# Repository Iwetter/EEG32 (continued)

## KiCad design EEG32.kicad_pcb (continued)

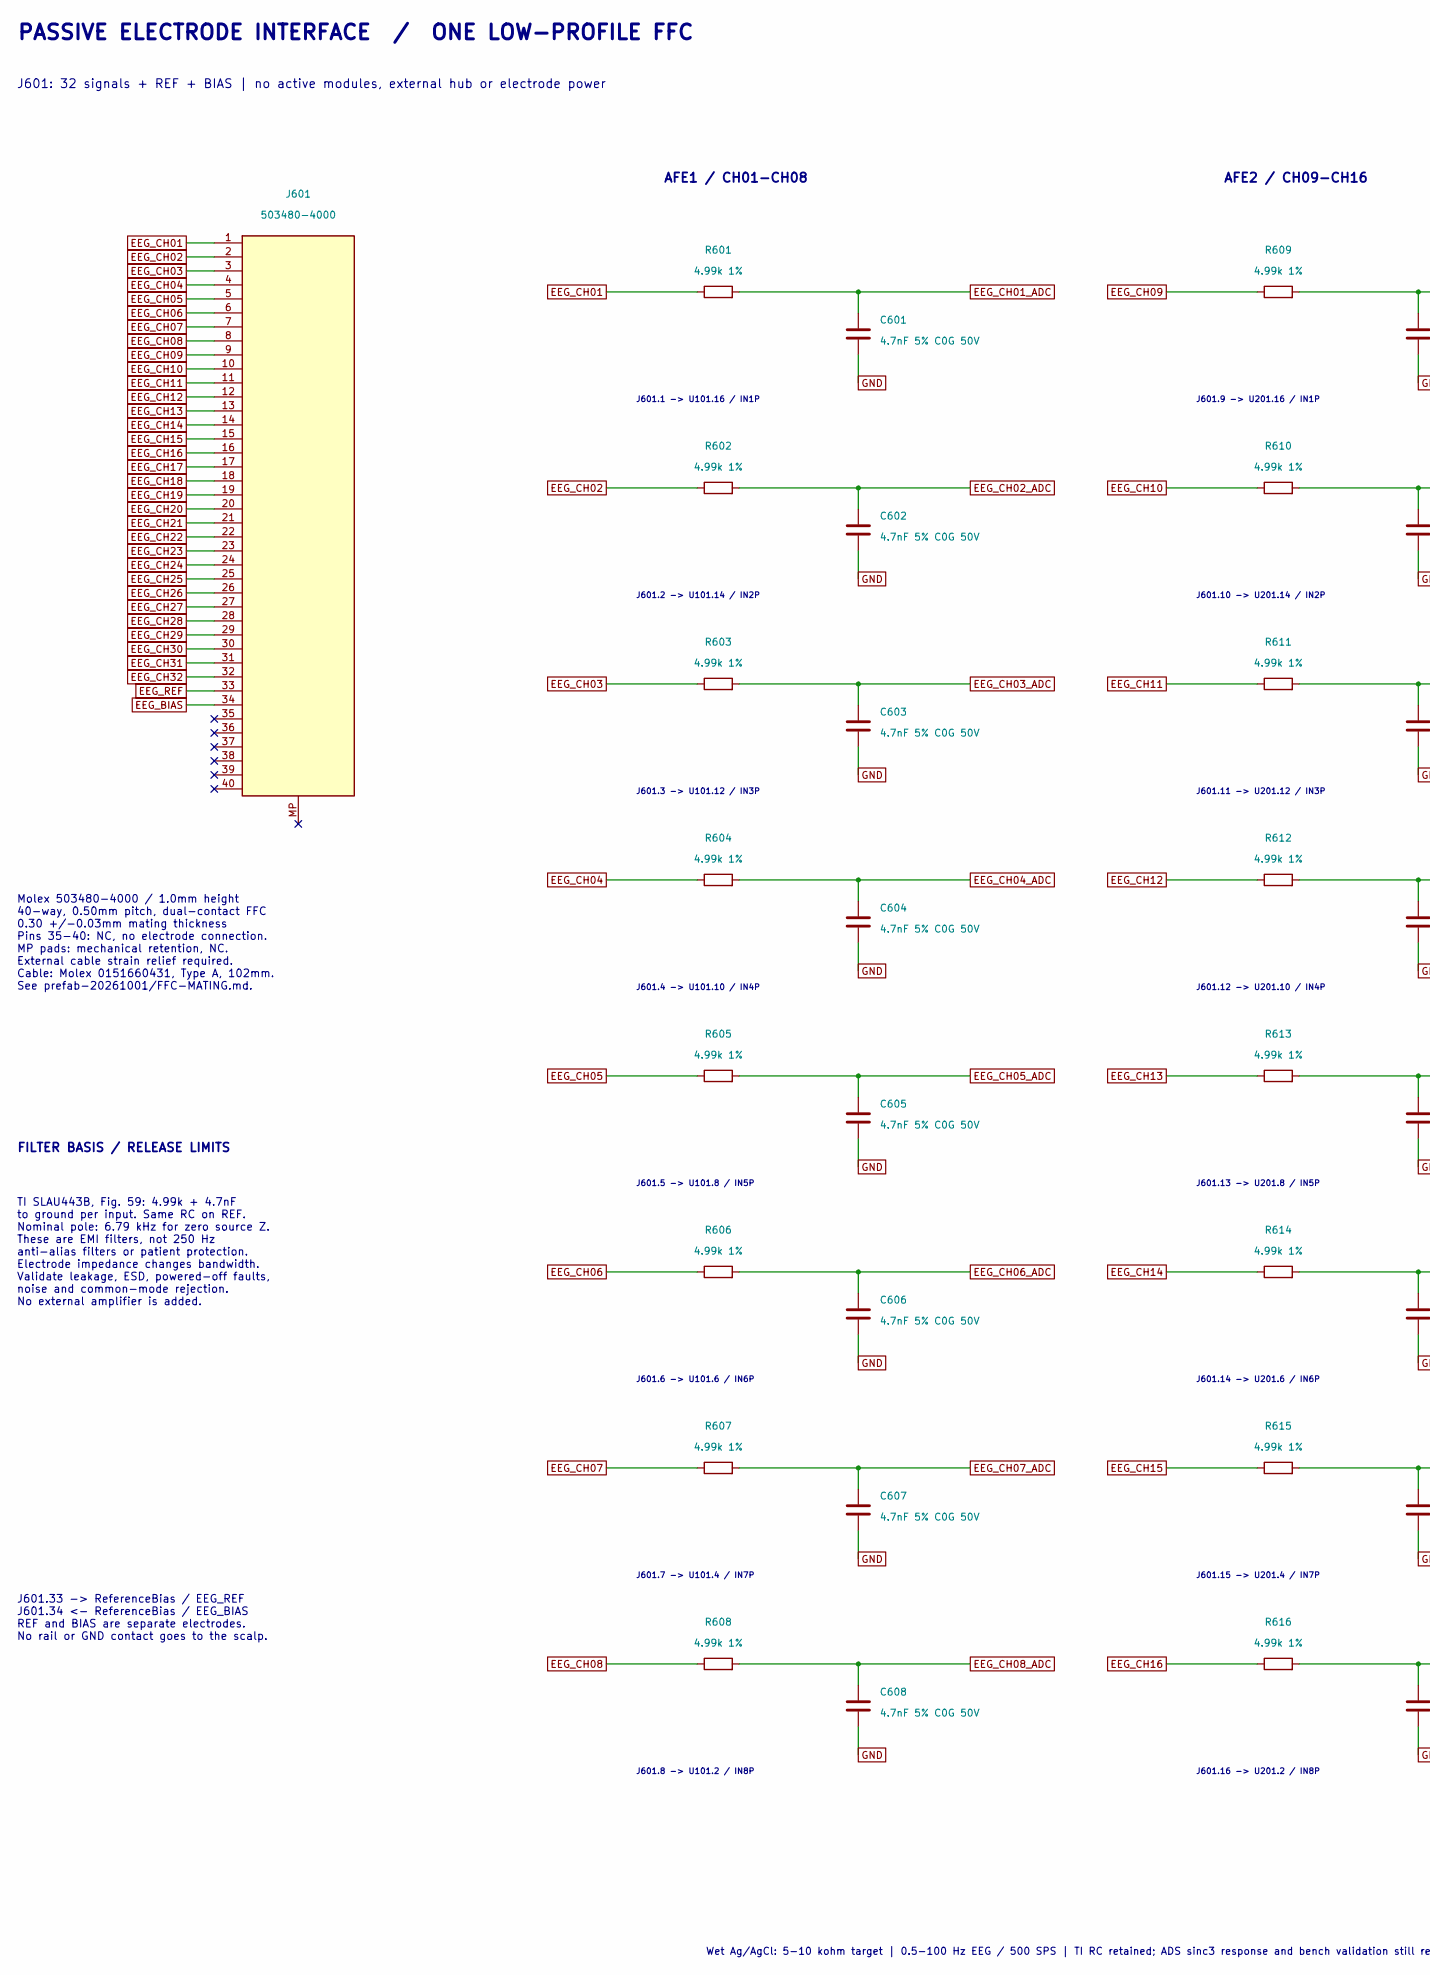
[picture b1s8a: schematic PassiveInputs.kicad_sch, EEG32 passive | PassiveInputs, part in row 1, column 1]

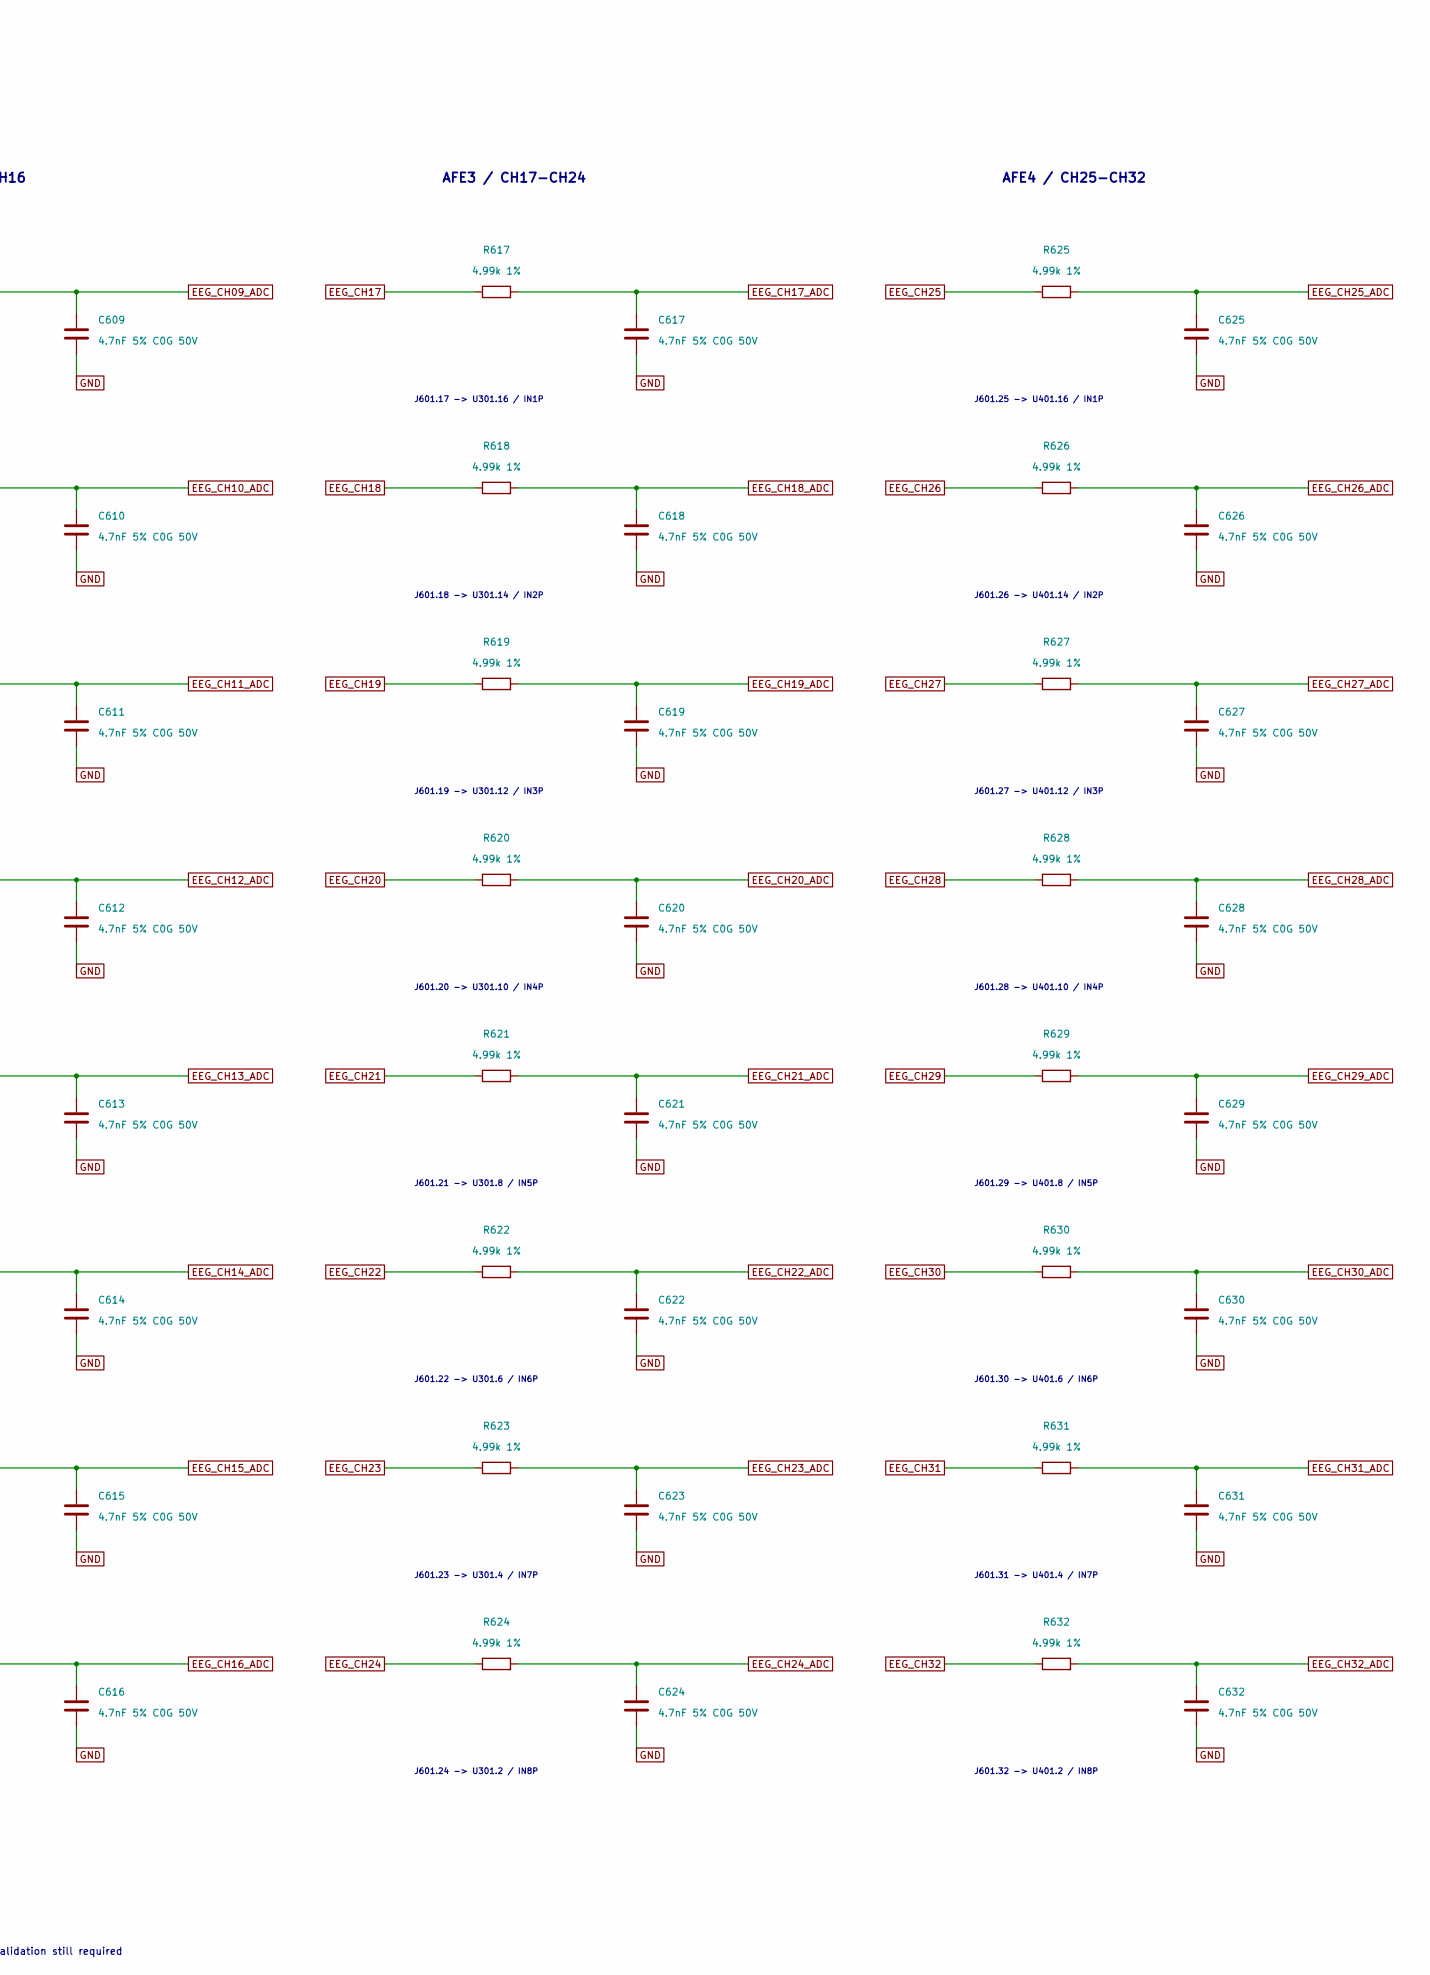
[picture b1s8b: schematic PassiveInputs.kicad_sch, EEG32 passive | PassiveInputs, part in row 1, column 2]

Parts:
C601, C602, C603, C604, C605, C606, C607, C608, C609, C610, C611, C612, C613, C614, C615, C616, C617, C618, C619, C620, C621, C622, C623, C624, C625, C626, C627, C628, C629, C630, C631, C632: 4.7nF 5% C0G 50V; C0603; MPN GRM1885C1H472JA01D
J601: 503480-4000; Molex_503480-4000_1x40_P0.50mm_Horizontal; MPN 503480-4000
R601, R602, R603, R604, R605, R606, R607, R608, R609, R610, R611, R612, R613, R614, R615, R616, R617, R618, R619, R620, R621, R622, R623, R624, R625, R626, R627, R628, R629, R630, R631, R632: 4.99k 1%; R0402; MPN RC0402FR-074K99L

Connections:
EEG_BIAS: J601.34; also elsewhere on the board
EEG_CH01: J601.1, R601.1
EEG_CH01_ADC: C601.1, R601.2; also elsewhere on the board
EEG_CH02: J601.2, R602.1
EEG_CH02_ADC: C602.1, R602.2; also elsewhere on the board
EEG_CH03: J601.3, R603.1
EEG_CH03_ADC: C603.1, R603.2; also elsewhere on the board
EEG_CH04: J601.4, R604.1
EEG_CH04_ADC: C604.1, R604.2; also elsewhere on the board
EEG_CH05: J601.5, R605.1
EEG_CH05_ADC: C605.1, R605.2; also elsewhere on the board
EEG_CH06: J601.6, R606.1
EEG_CH06_ADC: C606.1, R606.2; also elsewhere on the board
EEG_CH07: J601.7, R607.1
EEG_CH07_ADC: C607.1, R607.2; also elsewhere on the board
EEG_CH08: J601.8, R608.1
EEG_CH08_ADC: C608.1, R608.2; also elsewhere on the board
EEG_CH09: J601.9, R609.1
EEG_CH09_ADC: C609.1, R609.2; also elsewhere on the board
EEG_CH10: J601.10, R610.1
EEG_CH10_ADC: C610.1, R610.2; also elsewhere on the board
EEG_CH11: J601.11, R611.1
EEG_CH11_ADC: C611.1, R611.2; also elsewhere on the board
EEG_CH12: J601.12, R612.1
EEG_CH12_ADC: C612.1, R612.2; also elsewhere on the board
EEG_CH13: J601.13, R613.1
EEG_CH13_ADC: C613.1, R613.2; also elsewhere on the board
EEG_CH14: J601.14, R614.1
EEG_CH14_ADC: C614.1, R614.2; also elsewhere on the board
EEG_CH15: J601.15, R615.1
EEG_CH15_ADC: C615.1, R615.2; also elsewhere on the board
EEG_CH16: J601.16, R616.1
EEG_CH16_ADC: C616.1, R616.2; also elsewhere on the board
EEG_CH17: J601.17, R617.1
EEG_CH17_ADC: C617.1, R617.2; also elsewhere on the board
EEG_CH18: J601.18, R618.1
EEG_CH18_ADC: C618.1, R618.2; also elsewhere on the board
EEG_CH19: J601.19, R619.1
EEG_CH19_ADC: C619.1, R619.2; also elsewhere on the board
EEG_CH20: J601.20, R620.1
EEG_CH20_ADC: C620.1, R620.2; also elsewhere on the board
EEG_CH21: J601.21, R621.1
EEG_CH21_ADC: C621.1, R621.2; also elsewhere on the board
EEG_CH22: J601.22, R622.1
EEG_CH22_ADC: C622.1, R622.2; also elsewhere on the board
EEG_CH23: J601.23, R623.1
EEG_CH23_ADC: C623.1, R623.2; also elsewhere on the board
EEG_CH24: J601.24, R624.1
EEG_CH24_ADC: C624.1, R624.2; also elsewhere on the board
EEG_CH25: J601.25, R625.1
EEG_CH25_ADC: C625.1, R625.2; also elsewhere on the board
EEG_CH26: J601.26, R626.1
EEG_CH26_ADC: C626.1, R626.2; also elsewhere on the board
EEG_CH27: J601.27, R627.1
EEG_CH27_ADC: C627.1, R627.2; also elsewhere on the board
EEG_CH28: J601.28, R628.1
EEG_CH28_ADC: C628.1, R628.2; also elsewhere on the board
EEG_CH29: J601.29, R629.1
EEG_CH29_ADC: C629.1, R629.2; also elsewhere on the board
EEG_CH30: J601.30, R630.1
EEG_CH30_ADC: C630.1, R630.2; also elsewhere on the board
EEG_CH31: J601.31, R631.1
EEG_CH31_ADC: C631.1, R631.2; also elsewhere on the board
EEG_CH32: J601.32, R632.1
EEG_CH32_ADC: C632.1, R632.2; also elsewhere on the board
EEG_REF: J601.33; also elsewhere on the board
GND: C601.2, C602.2, C603.2, C604.2, C605.2, C606.2, C607.2, C608.2, C609.2, C610.2, C611.2, C612.2, C613.2, C614.2, C615.2, C616.2, C617.2, C618.2, C619.2, C620.2, C621.2, C622.2, C623.2, C624.2, C625.2, C626.2, C627.2, C628.2, C629.2, C630.2, C631.2, C632.2; also elsewhere on the board

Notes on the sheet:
PASSIVE ELECTRODE INTERFACE / ONE LOW-PROFILE FFC
J601: 32 signals + REF + BIAS | no active modules, external hub or electrode power
Molex 503480-4000 / 1.0mm height 40-way, 0.50mm pitch, dual-contact FFC 0.30 +/-0.03mm mating thickness Pins 35-40: NC, no electrode connection. MP pads: mechanical retention, NC. External cable strain relief required. Cable: Molex 0151660431, Type A, 102mm. See prefab-20261001/FFC-MATING.md.
FILTER BASIS / RELEASE LIMITS
TI SLAU443B, Fig. 59: 4.99k + 4.7nF to ground per input. Same RC on REF. Nominal pole: 6.79 kHz for zero source Z. These are EMI filters, not 250 Hz anti-alias filters or patient protection. Electrode impedance changes bandwidth. Validate leakage, ESD, powered-off faults, noise and common-mode reje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
J601.33 -> ReferenceBias / EEG_REF J601.34 <- ReferenceBias / EEG_BIAS REF and BIAS are separate electrodes. No rail or GND contact goes to the scalp.
AFE1 / CH01-CH08
J601.1 -> U101.16 / IN1P
J601.2 -> U101.14 / IN2P
J601.3 -> U101.12 / IN3P
J601.4 -> U101.10 / IN4P
J601.5 -> U101.8 / IN5P
J601.6 -> U101.6 / IN6P
J601.7 -> U101.4 / IN7P
J601.8 -> U101.2 / IN8P
AFE2 / CH09-CH16
J601.9 -> U201.16 / IN1P
J601.10 -> U201.14 / IN2P
J601.11 -> U201.12 / IN3P
J601.12 -> U201.10 / IN4P
J601.13 -> U201.8 / IN5P
J601.14 -> U201.6 / IN6P
J601.15 -> U201.4 / IN7P
J601.16 -> U201.2 / IN8P
AFE3 / CH17-CH24
J601.17 -> U301.16 / IN1P
J601.18 -> U301.14 / IN2P
J601.19 -> U301.12 / IN3P
J601.20 -> U301.10 / IN4P
J601.21 -> U301.8 / IN5P
J601.22 -> U301.6 / IN6P
J601.23 -> U301.4 / IN7P
J601.24 -> U301.2 / IN8P
AFE4 / CH25-CH32
J601.25 -> U401.16 / IN1P
J601.26 -> U401.14 / IN2P
J601.27 -> U401.12 / IN3P
J601.28 -> U401.10 / IN4P
J601.29 -> U401.8 / IN5P
J601.30 -> U401.6 / IN6P

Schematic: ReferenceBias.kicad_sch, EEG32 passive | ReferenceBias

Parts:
C633: 4.7nF 5% C0G 50V; C0603; MPN GRM1885C1H472JA01D
R633, R634: 4.99k 1%; R0402; MPN RC0402FR-074K99L

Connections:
BIAS_DRIVE: R634.1; also elsewhere on the board
EEG_BIAS: R634.2; also elsewhere on the board
EEG_REF: R633.1; also elsewhere on the board
EEG_REF_ADC: C633.1, R633.2; also elsewhere on the board
GND: C633.2; also elsewhere on the board

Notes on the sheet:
SHARED REF / SEPARATE BIAS
Passive common-reference montage. No local electrode buffers; no REF/BIAS short.
J601.33 / passive REF
U101/U201/U301/U401: pin 17 / SRB1 MISC1.SRB1 = 1; SRB2 remains unused. TP7 measures the filtered shared reference.
Unbuffered shared REF retained: validate aggregate input loading and lead-off configuration for 32 channels. One common REF filter; do not add 32 parallel filter capacitors to this electrode. TI EVM default directly selects REF_ELEC to SRB1 (JP8); its optional buffer is not populated here.
U101 BIASOUT, pin 63 Existing 1M || 1nF feedback remains before R634.
J601.34 / separate BIAS electrode 4.99k is TI EVM R10 value; it is not a validated patient-current limiter.
FIRMWARE + VALIDATION
Enable only U101 BIAS amplifier; slave BIASOUT pins remain NC. Preserve shared BIAS_SUM and BIASIN. Select BIAS sense channels deliberately. Validate stability with electrode/cable impedance and disconnect faults. At +5VA, internal BIASREF targets mid-supply. REF is neither GND nor the ADS VREFP co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
PROTECTION RELEASE HOLD: RC networks reduce input current/EMI but do not establish ESD, defibrillator, isolation, leakage or single-fault safety. No human connection until supervisor/electrical safety validation.

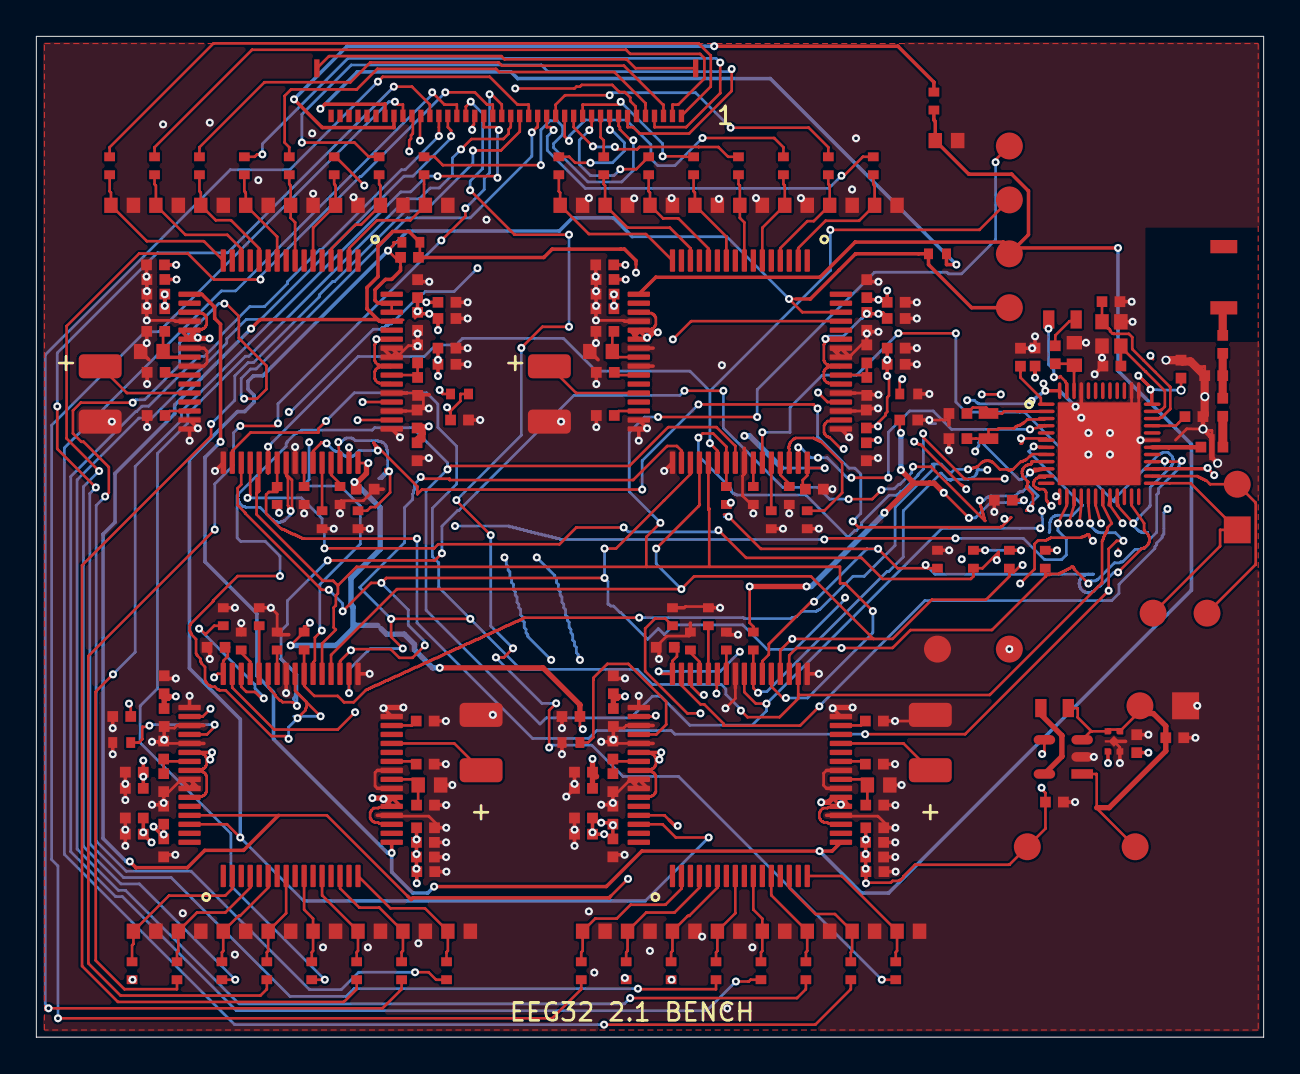
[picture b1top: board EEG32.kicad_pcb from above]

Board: 4 copper layers, 68.3 x 55.7 mm, 225 parts (1 on the bottom side), 148 nets.

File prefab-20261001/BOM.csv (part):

Reference,Value,Footprint,Manufacturer,MPN,Electrical_Spec,Datasheet,Qualification
C1,20pF,EEG32:C0402,Murata,GJM1555C1H200FB01D,20pF; +/-1%; C0G; 50V; high-Q; 0402,https://www.murata.com/en-global/products/productdetail?part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,Exact part specified; bench/process qualification pending
C2,20pF,EEG32:C0402,Murata,GJM1555C1H200FB01D,20pF; +/-1%; C0G; 50V; high-Q; 0402,https://www.murata.com/en-global/products/productdetail?part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,Exact part specified; bench/process qualification pending
C3,12pF,EEG32:C0402,KYOCERA AVX,04025U120FAT2A,12pF; +/-1%; C0G/NP0 ultra-low ESR; 50V; 0402,https://www.kyocera-avx.com/docs/catalogs/U-Series.pdf,Exact part specified; bench/process qualification pending
C4,12pF,EEG32:C0402,KYOCERA AVX,04025U120FAT2A,12pF; +/-1%; C0G/NP0 ultra-low ESR; 50V; 0402,https://www.kyocera-avx.com/docs/catalogs/U-Series.pdf,Exact part specified; bench/process qualification pending
C5,100nF,EEG32:C0402,Taiyo Yuden,MSAST105SB5104KFNA01,100nF; +/-10%; X5R; 25V; 0402,https://ds.yuden.co.jp/TYCOMPAS/ap/detail?pn=MSAST105SB5104K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,Manufacturer renamed TMK105BJ104KV-F; same nominal value/size; no RF substitution implied
C6,100pF,EEG32:C0402,Yageo,CC0402FRNPO9BN101,100pF; +/-1%; NP0; 50V; 0402,https://www.yageo.com/en/Product/Index/mlcc/general_purpose/cc,Exact part specified; bench/process qualification pending
C7,1pF,EEG32:C0402,Murata,GCQ1555C1H1R0BB01D,1pF; +/-0.1pF; C0G; 50V; high-Q; 0402,https://www.murata.com/en-global/products/productdetail?part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,Exact part specified; bench/process qualification pending
C8,1uF,EEG32:C0603,Murata,GRM188R61A105KA61D,1uF; +/-10%; X5R; 10VDC; 0603; -55..85C,https://www.murata.com/en-global/products/productdetail?part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,nRF DEC4 1uF nominal; qualify DC-bias effective value at1.3V
C9,100nF,EEG32:C0402,Taiyo Yuden,MSAST105SB5104KFNA01,100nF; +/-10%; X5R; 25V; 0402,https://ds.yuden.co.jp/TYCOMPAS/ap/detail?pn=MSAST105SB5104K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,Manufacturer renamed TMK105BJ104KV-F; same nominal value/size; no RF substitution implied
C10,4.7uF,EEG32:C0402,Murata,GRM155R60J475ME87D,4.7uF; +/-20%; X5R; 6.3VDC; 0402; -55..85C,https://www.murata.com/en-global/products/productdetail?part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,Exact part specified; bench/process qualification pending
C11,100nF,EEG32:C0402,Murata,GRM155R71C104KA88D,100nF; +/-10%; X7R; 16VDC; 0402; -55..125C,https://www.murata.com/en-global/products/productdetail?part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,Exact part specified; bench/process qualification pending
C12,10uF,EEG32:C0402,Murata,GRM155R61A106ME11D,10uF; +/-20%; X5R; 10VDC; 0402; -55..85C,https://www.murata.com/en-global/products/productdetail?part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,S-1318 output/input: >=1uF effective across rail/temperature/tolerance/aging; vendor DC-bias evidence required
C13,10uF,EEG32:C0402,Murata,GRM155R61A106ME11D,10uF; +/-20%; X5R; 10VDC; 0402; -55..85C,https://www.murata.com/en-global/products/productdetail?part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,S-1318 output/input: >=1uF effective across rail/temperature/tolerance/aging; vendor DC-bias evidence required
C14,10uF,EEG32:C0402,Murata,GRM155R61A106ME11D,10uF; +/-20%; X5R; 10VDC; 0402; -55..85C,https://www.murata.com/en-global/products/productdetail?part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,Boost output: preserve10uF nominal; qualify effective capacitance/ESR against XC9140 recommended circuit and loaded startup
C15,100nF,EEG32:C0402,Murata,GRM155R71C104KA88D,100nF; +/-10%; X7R; 16VDC; 0402; -55..125C,https://www.murata.com/en-global/products/productdetail?part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,Exact part specified; bench/process qualification pending
C101,100uF 6.3V TANT,EEG32:CP_EIA-3528-21_Kemet-B,KEMET,T491B107K006AT,100uF; +/-10%; tantalum; 6.3VDC; B/3528; ESR <=2.0ohm at100kHz; polarized,https://content.kemet.com/datasheets/KEM_T2005_T491.pdf,VCAP1 part retained; check anode/polarity and surge/derating
C102,1uF,EEG32:C0402,Murata,GRM155R61A105KE15D,1uF; +/-10%; X5R; 10VDC; 0402; -55..85C,https://www.murata.com/en-global/products/productdetail?part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,Exact part specified; bench/process qualification pending
C103,1nF,EEG32:C0402,Murata,GRM1555C1H102JA01D,1nF; +/-5%; C0G; 50VDC; 0402; -55..125C,https://www.murata.com/en-global/products/productdetail?part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,Nominal BIAS compensation unchanged; stability qualification required
C104,1uF,EEG32:C0402,Murata,GRM155R61A105KE15D,1uF; +/-10%; X5R; 10VDC; 0402; -55..85C,https://www.murata.com/en-global/products/productdetail?part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,Exact part specified; bench/process qualification pending
C105,100nF,EEG32:C0402,Murata,GRM155R71C104KA88D,100nF; +/-10%; X7R; 16VDC; 0402; -55..125C,https://www.murata.com/en-global/products/productdetail?part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,Exact part specified; bench/process qualification pending
C106,1uF,EEG32:C0402,Murata,GRM155R61A105KE15D,1uF; +/-10%; X5R; 10VDC; 0402; -55..85C,https://www.murata.com/en-global/products/productdetail?part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,Exact part specified; bench/process qualification pending
C107,100nF,EEG32:C0402,Murata,GRM155R71C104KA88D,100nF; +/-10%; X7R; 16VDC; 0402; -55..125C,https://www.murata.com/en-global/products/productdetail?part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,Exact part specified; bench/process qualification pending
C108,1uF,EEG32:C0402,Murata,GRM155R61A105KE15D,1uF; +/-10%; X5R; 10VDC; 0402; -55..85C,https://www.murata.com/en-global/products/productdetail?part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,Exact part specified; bench/process qualification pending
C109,100nF,EEG32:C0402,Murata,GRM155R71C104KA88D,100nF; +/-10%; X7R; 16VDC; 0402; -55..125C,https://www.murata.com/en-global/products/productdetail?part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,Exact part specified; bench/process qualification pending
C110,1uF,EEG32:C0402,Murata,GRM155R61A105KE15D,1uF; +/-10%; X5R; 10VDC; 0402; -55..85C,https://www.murata.com/en-global/products/productdetail?part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,Exact part specified; bench/process qualification pending
C111,100nF,EEG32:C0402,Murata,GRM155R71C104KA88D,100nF; +/-10%; X7R; 16VDC; 0402; -55..125C,https://www.murata.com/en-global/products/productdetail?part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,Exact part specified; bench/process qualification pending
C112,100nF,EEG32:C0402,Murata,GRM155R71C104KA88D,100nF; +/-10%; X7R; 16VDC; 0402; -55..125C,https://www.murata.com/en-global/products/productdetail?part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,Exact part specified; bench/process qualification pending
C113,10uF,EEG32:C0603,Murata,GRM188R61A106KE69D,10uF; +/-10%; X5R; 10VDC; 0603; -55..85C,https://www.murata.com/en-global/products/productdetail?part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,Specified ADS VREFP capacitor; effective capacitance >= datasheet requirement under bias required
C114,100nF,EEG32:C0402,Murata,GRM155R71C104KA88D,100nF; +/-10%; X7R; 16VDC; 0402; -55..125C,https://www.murata.com/en-global/products/productdetail?part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,Exact part specified; bench/process qualification pending
C115,1uF,EEG32:C0402,Murata,GRM155R61A105KE15D,1uF; +/-10%; X5R; 10VDC; 0402; -55..85C,https://www.murata.com/en-global/products/productdetail?part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,Exact part specified; bench/process qualification pending
C116,1uF,EEG32:C0402,Murata,GRM155R61A105KE15D,1uF; +/-10%; X5R; 10VDC; 0402; -55..85C,https://www.murata.com/en-global/products/productdetail?part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,Exact part specified; bench/process qualification pending
C117,1uF,EEG32:C0402,Murata,GRM155R61A105KE15D,1uF; +/-10%; X5R; 10VDC; 0402; -55..85C,https://www.murata.com/en-global/products/productdetail?part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,Exact part specified; bench/process qualification pending
C118,100nF,EEG32:C0402,Murata,GRM155R71C104KA88D,100nF; +/-10%; X7R; 16VDC; 0402; -55..125C,https://www.murata.com/en-global/products/productdetail?part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,Exact part specified; bench/process qualification pending
C119,1uF,EEG32:C0402,Murata,GRM155R61A105KE15D,1uF; +/-10%; X5R; 10VDC; 0402; -55..85C,https://www.murata.com/en-global/products/productdetail?part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,Exact part specified; bench/process qualification pending
C120,100nF,EEG32:C0402,Murata,GRM155R71C104KA88D,100nF; +/-10%; X7R; 16VDC; 0402; -55..125C,https://www.murata.com/en-global/products/productdetail?part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,Exact part specified; bench/process qualification pending
C121,1uF,EEG32:C0402,Murata,GRM155R61A105KE15D,1uF; +/-10%; X5R; 10VDC; 0402; -55..85C,https://www.murata.com/en-global/products/productdetail?part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,Exact part specified; bench/process qualification pending
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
